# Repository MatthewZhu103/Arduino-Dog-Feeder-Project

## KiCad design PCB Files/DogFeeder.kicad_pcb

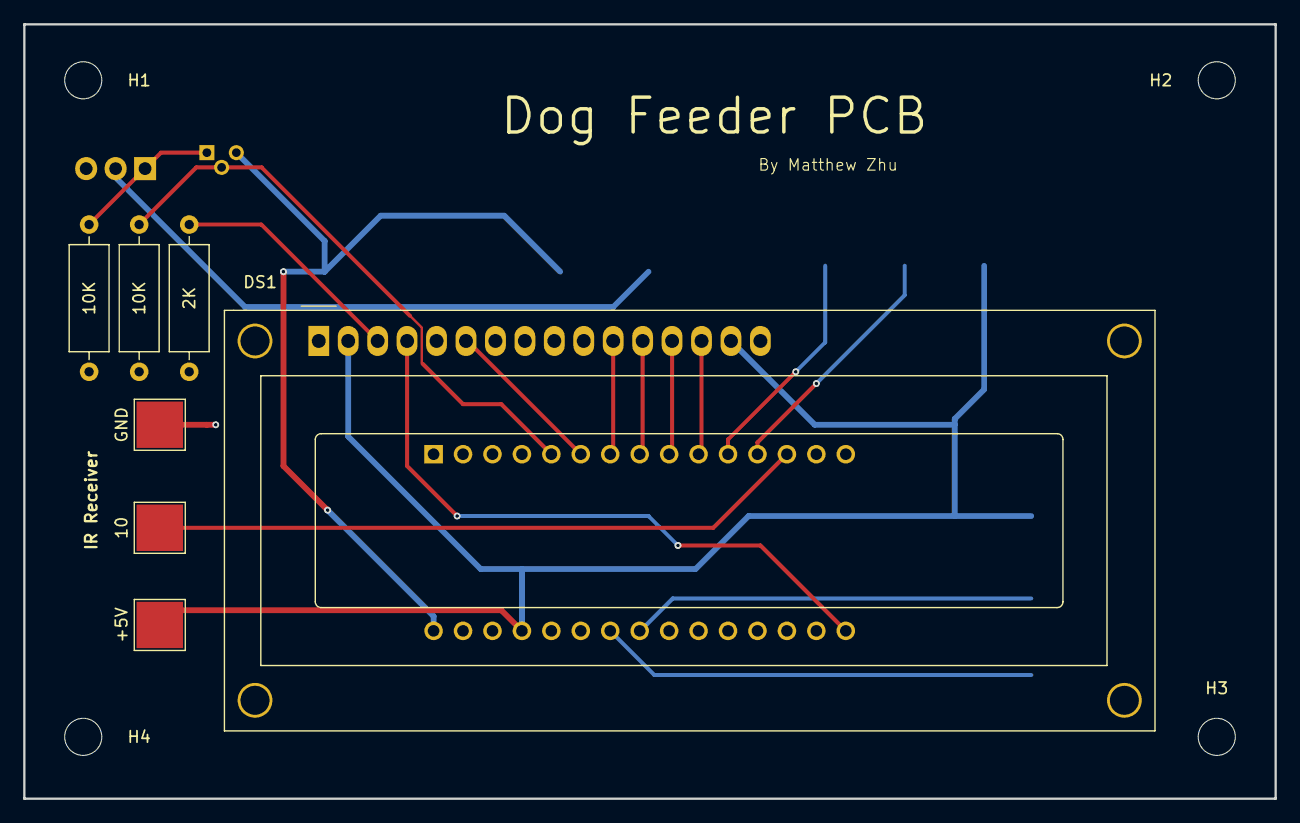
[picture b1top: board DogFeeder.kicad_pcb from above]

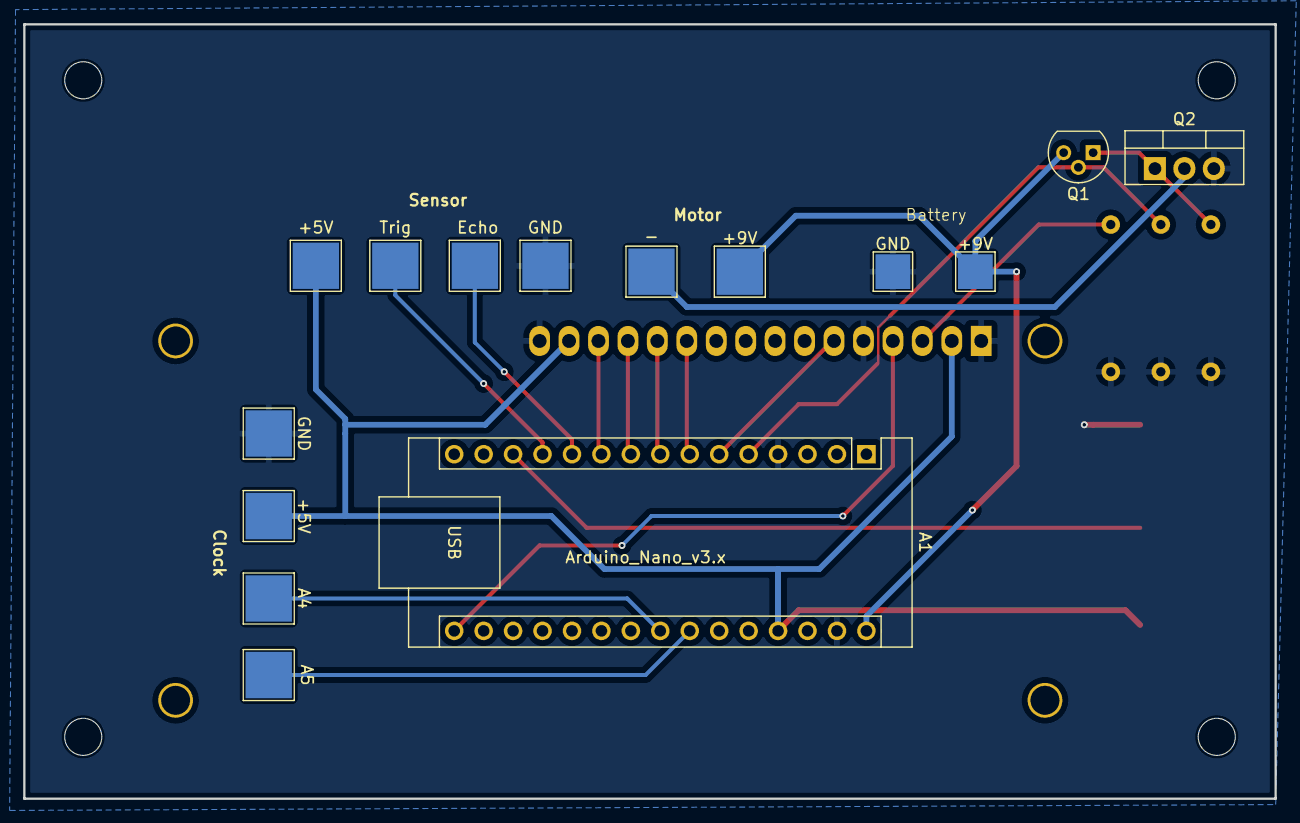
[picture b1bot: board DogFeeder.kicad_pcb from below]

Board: 2 copper layers, 107.9 x 66.8 mm, 26 parts (15 on the bottom side), 18 nets.

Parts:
10: TestPoint; TestPoint_Pad_4.0x4.0mm
10K, 10K#2: 10K; R_Axial_DIN0309_L9.0mm_D3.2mm_P12.70mm_Horizontal
+5V, +5V#2, +9V: TestPoint; TestPoint_Pad_4.0x4.0mm
+9V#2: TestPoint; TestPoint_Pad_3.0x3.0mm
-: TestPoint; TestPoint_Pad_4.0x4.0mm
A1: Arduino_Nano_v3.x; Arduino_Nano
A4: TestPoint; TestPoint_Pad_4.0x4.0mm
DS1: WC1602A
Echo: TestPoint; TestPoint_Pad_4.0x4.0mm
GND: TestPoint; TestPoint_Pad_4.0x4.0mm
GND#2: TestPoint; TestPoint_Pad_4.0x4.0mm
GND#3: TestPoint; TestPoint_Pad_3.0x3.0mm
H1, H2, H3, H4: MountingHole; MountingHole_3.2mm_M3
Q1: 2N2219; TO-92
Q2: IRF540N; TO-220-3_Vertical
R4: 2k; R_Axial_DIN0309_L9.0mm_D3.2mm_P12.70mm_Horizontal
TP12, TP14, TP15: TestPoint; TestPoint_Pad_4.0x4.0mm
Trig: TestPoint; TestPoint_Pad_4.0x4.0mm

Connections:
+5V: +5V.1, +5V#2.1, A1.27 (+5V), DS1.2 (VDD), DS1.15 (LED(+)), TP14.1
+9V: +9V.1, +9V#2.1, A1.30 (VIN), Q1.3 (C)
/2: 10K.1, A1.5 (D2), Q1.2 (B)
/3: A1.6 (D3), DS1.6 (E)
/4: A1.7 (D4), DS1.11 (D4)
/5: A1.8 (D5), DS1.12 (D5)
/6: A1.9 (D6), DS1.13 (D6)
/7: A1.10 (D7), DS1.14 (D7)
/8: A1.11 (D8), Echo.1
/9: A1.12 (D9), Trig.1
/10: 10.1, A1.13 (D10)
/13: A1.16 (D13), DS1.4 (RS)
/A4: A1.23 (A4), A4.1
/A5: A1.24 (A5), TP12.1
GND: 10K.2, 10K#2.2, A1.4 (GND), A1.29 (GND), DS1.1 (VSS), DS1.5 (R/W), DS1.16 (LED(-)), GND.1, GND#2.1, GND#3.1, Q2.3 (S), R4.2, TP15.1
unnamed: -.1, Q2.2 (D)
unnamed: DS1.3 (VO), R4.1
unnamed: 10K#2.1, Q1.1 (E), Q2.1 (G)

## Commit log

2023-08-16 DogFeederCode.ino uploaded to repository
2023-08-16 Put text in TrialDocument.txt
2023-08-28 Added PCB Files
